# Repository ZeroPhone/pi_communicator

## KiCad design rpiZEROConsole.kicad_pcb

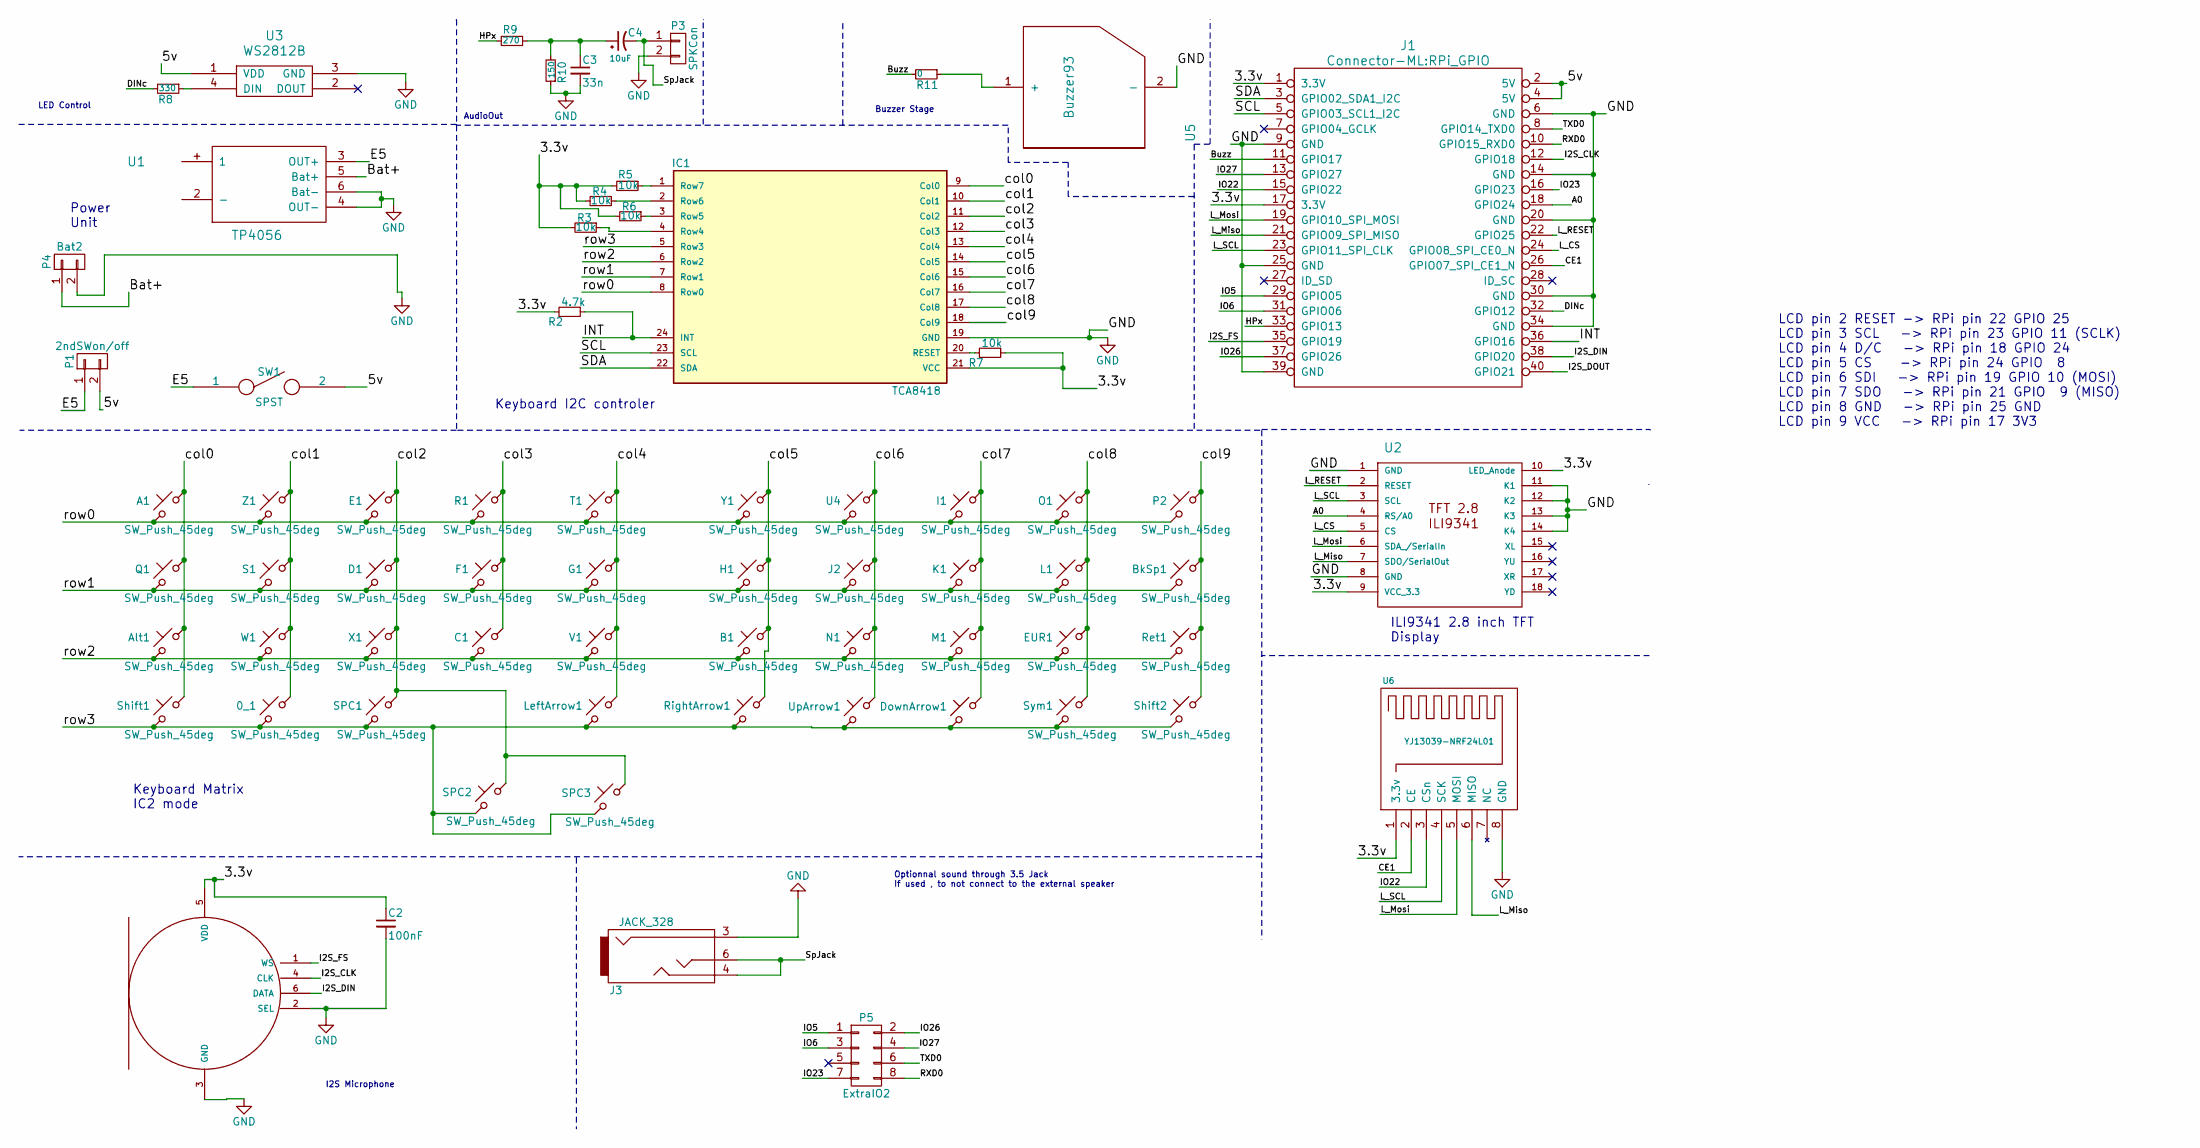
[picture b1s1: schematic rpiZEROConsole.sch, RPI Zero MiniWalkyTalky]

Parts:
0_1: SW_Push_45deg; SW_TP1003
A1: SW_Push_45deg; SW_TP1003
Alt1: SW_Push_45deg; SW_TP1003
B1: SW_Push_45deg; SW_TP1003
BkSp1: SW_Push_45deg; SW_TP1003
C1: SW_Push_45deg; SW_TP1003
C2: 100nF; C_1206_HandSoldering
C3: 33n; C_1206_HandSoldering
C4: 10uF; CP_Elec_6.3x5.3
D1: SW_Push_45deg; SW_TP1003
DownArrow1: SW_Push_45deg; SW_TP1003
E1: SW_Push_45deg; SW_TP1003
EUR1: SW_Push_45deg; SW_TP1003
F1: SW_Push_45deg; SW_TP1003
G1: SW_Push_45deg; SW_TP1003
H1: SW_Push_45deg; SW_TP1003
I1: SW_Push_45deg; SW_TP1003
IC1: TCA8418; TCA8418-WQFN-24-1EP_4x4mm
J1: Connector-ML:RPi_GPIO; Raspberry_Pi_Zero_SMD
J2: SW_Push_45deg; SW_TP1003
J3: JACK_328; Jack_JP328
K1: SW_Push_45deg; SW_TP1003
L1: SW_Push_45deg; SW_TP1003
LeftArrow1: SW_Push_45deg; SW_TP1003
M1: SW_Push_45deg; SW_TP1003
M2: MEMS_MIC_SPH0645LM4H-BI2S; MIC_SPH0645LM4H-B
N1: SW_Push_45deg; SW_TP1003
O1: SW_Push_45deg; SW_TP1003
P1: 2ndSWon/off; Socket_Strip_Straight_1x02_Pitch2.54mm
P2: SW_Push_45deg; SW_TP1003
P3: SPKCon; Socket_Strip_Straight_1x02_Pitch2.54mm
P4: Bat2; Socket_Strip_Straight_1x02_Pitch2.54mm
P5: ExtraIO2; 2x4SMD
Q1: SW_Push_45deg; SW_TP1003
R1: SW_Push_45deg; SW_TP1003
R2: 4.7k; R_1206_HandSoldering
R3, R4, R5, R6, R7: 10k; R_1206_HandSoldering
R8: 330; R_1206_HandSoldering
R9: 270; R_1206_HandSoldering
R10: 150; R_1206_HandSoldering
R11: 0; R_1206_HandSoldering
Ret1: SW_Push_45deg; SW_TP1003
RightArrow1: SW_Push_45deg; SW_TP1003
S1: SW_Push_45deg; SW_TP1003
SPC1, SPC2, SPC3: SW_Push_45deg; SW_TP1003
SW1: SPST; SW_SPDT_PCM12
Shift1, Shift2: SW_Push_45deg; SW_TP1003
Sym1: SW_Push_45deg; SW_TP1003
T1: SW_Push_45deg; SW_TP1003
U1: TP4056; TP4056-18650CMS
U2: ILI9341_28_18PINS; ILI9341_2.8
U3: WS2812B
U4: SW_Push_45deg; SW_TP1003
U5: Buzzer93; BuzzerActive2
U6: YJ13039-NRF24L01; YJ-13039-NRF24L01
UpArrow1: SW_Push_45deg; SW_TP1003
V1: SW_Push_45deg; SW_TP1003
W1: SW_Push_45deg; SW_TP1003
X1: SW_Push_45deg; SW_TP1003
Y1: SW_Push_45deg; SW_TP1003
Z1: SW_Push_45deg; SW_TP1003

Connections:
/3.3v: C2.1, IC1.21 (VCC), J1.1 (3.3V), J1.17 (3.3V), M2.5 (VDD), R2.2, R3.2, R4.2, R5.2, R6.2, R7.1, U2.9 (VCC_3.3), U2.10 (LED_Anode), U6.1 (3.3v)
/5v: J1.2 (5V), J1.4 (5V), P1.2, SW1.2, U3.1 (VDD); also elsewhere on the board
/A0: J1.18 (GPIO24), U2.4 (RS/A0)
/Bat+: P4.1, U1.5 (Bat+); also elsewhere on the board
/Buzz: J1.11 (GPIO17), R11.2
/CE1: J1.26 (GPIO07_SPI_CE1_N), U6.2 (CE)
/DINc: J1.32 (GPIO12), R8.2
/E5: P1.1, SW1.1, U1.3 (OUT+); also elsewhere on the board
/HPx: J1.33 (GPIO13), R9.2
/I2S_CLK: J1.12 (GPIO18), M2.4 (CLK)
/I2S_DIN: J1.38 (GPIO20), M2.6 (DATA)
/I2S_FS: J1.35 (GPIO19), M2.1 (WS)
/INT: IC1.24 (INT), J1.36 (GPIO16), R2.1
/IO5: J1.29 (GPIO05), P5.1
/IO6: J1.31 (GPIO06), P5.3
/IO22: J1.15 (GPIO22), U6.3 (CSn)
/IO23: J1.16 (GPIO23), P5.7
/IO26: J1.37 (GPIO26), P5.2
/IO27: J1.13 (GPIO27), P5.4
/L_CS: J1.24 (GPIO08_SPI_CE0_N), U2.5 (CS)
/L_Miso: J1.21 (GPIO09_SPI_MISO), U2.7 (SDO/SerialOut), U6.6 (MISO)
/L_Mosi: J1.19 (GPIO10_SPI_MOSI), U2.6 (SDA_/SerialIn), U6.5 (MOSI)
/L_RESET: J1.22 (GPIO25), U2.2 (RESET)
/L_SCL: J1.23 (GPIO11_SPI_CLK), U2.3 (SCL), U6.4 (SCK)
/RXD0: J1.10 (GPIO15_RXD0), P5.8
/SCL: IC1.23 (SCL), J1.5 (GPIO03_SCL1_I2C)
/SDA: IC1.22 (SDA), J1.3 (GPIO02_SDA1_I2C)
/SpJack: C4.2, J3.4, J3.6, P3.1
/TXD0: J1.8 (GPIO14_TXD0), P5.6
/col0: A1.1, Alt1.1, IC1.9 (Col0), Q1.1, Shift1.1
/col1: 0_1.1, IC1.10 (Col1), S1.1, W1.1, Z1.1
/col2: D1.1, E1.1, IC1.11 (Col2), SPC1.1, SPC2.1, SPC3.1, X1.1
/col3: C1.1, F1.1, IC1.12 (Col3), R1.1
/col4: G1.1, IC1.13 (Col4), LeftArrow1.1, T1.1, V1.1
/col5: B1.1, H1.1, IC1.14 (Col5), RightArrow1.1, Y1.1
/col6: IC1.15 (Col6), J2.1, N1.1, U4.1, UpArrow1.1
/col7: DownArrow1.1, I1.1, IC1.16 (Col7), K1.1, M1.1
/col8: EUR1.1, IC1.17 (Col8), L1.1, O1.1, Sym1.1
/col9: BkSp1.1, IC1.18 (Col9), P2.1, Ret1.1, Shift2.1
/row0: A1.2, E1.2, I1.2, IC1.8 (Row0), O1.2, P2.2, R1.2, T1.2, U4.2, Y1.2, Z1.2
/row1: BkSp1.2, D1.2, F1.2, G1.2, H1.2, IC1.7 (Row1), J2.2, K1.2, L1.2, Q1.2, S1.2
/row2: Alt1.2, B1.2, C1.2, EUR1.2, IC1.6 (Row2), M1.2, N1.2, Ret1.2, V1.2, W1.2, X1.2
/row3: 0_1.2, DownArrow1.2, IC1.5 (Row3), LeftArrow1.2, RightArrow1.2, SPC1.2, SPC2.2, SPC3.2, Shift1.2, Shift2.2, Sym1.2, UpArrow1.2
GND: C2.2, C3.2, IC1.19 (GND), J1.6 (GND), J1.9 (GND), J1.14 (GND), J1.20 (GND), J1.25 (GND), J1.30 (GND), J1.34 (GND), J1.39 (GND), J3.3, M2.2 (SEL), M2.3 (GND), M2.P$1 (GND), P3.2, P4.2, R10.1, U1.4 (OUT-), U1.6 (Bat-), U2.1 (GND), U2.8 (GND), U2.11 (K1), U2.12 (K2), U2.13 (K3), U2.14 (K4), U3.3 (GND), U5.2 (-), U6.8 (GND); also elsewhere on the board
unnamed: C3.1, C4.1, R9.1, R10.2
unnamed: IC1.1 (Row7), R5.1
unnamed: IC1.2 (Row6), R4.1
unnamed: IC1.3 (Row5), R6.1
unnamed: IC1.4 (Row4), R3.1
unnamed: IC1.20 (RESET), R7.2
unnamed: R8.1, U3.4 (DIN)
unnamed: R11.1, U5.1 (+)

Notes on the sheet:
Power Unit
Keyboard Matrix IC2 mode
Keyboard I2C controler
ILI9341 2.8 inch TFT Display
LCD pin 2 RESET -> RPi pin 22 GPIO 25 LCD pin 3 SCL -> RPi pin 23 GPIO 11 (SCLK) LCD pin 4 D/C -> RPi pin 18 GPIO 24 LCD pin 5 CS -> RPi pin 24 GPIO 8 LCD pin 6 SDI -> RPi pin 19 GPIO 10 (MOSI) LCD pin 7 SDO -> RPi pin 21 GPIO 9 (MISO) LCD pin 8 GND -> RPi pin 25 GND LCD pin 9 VCC -> RPi pin 17 3V3
LED Control
Buzzer Stage
AudioOut
I2S Microphone
Optionnal sound through 3.5 Jack If used , to not connect to the external speaker

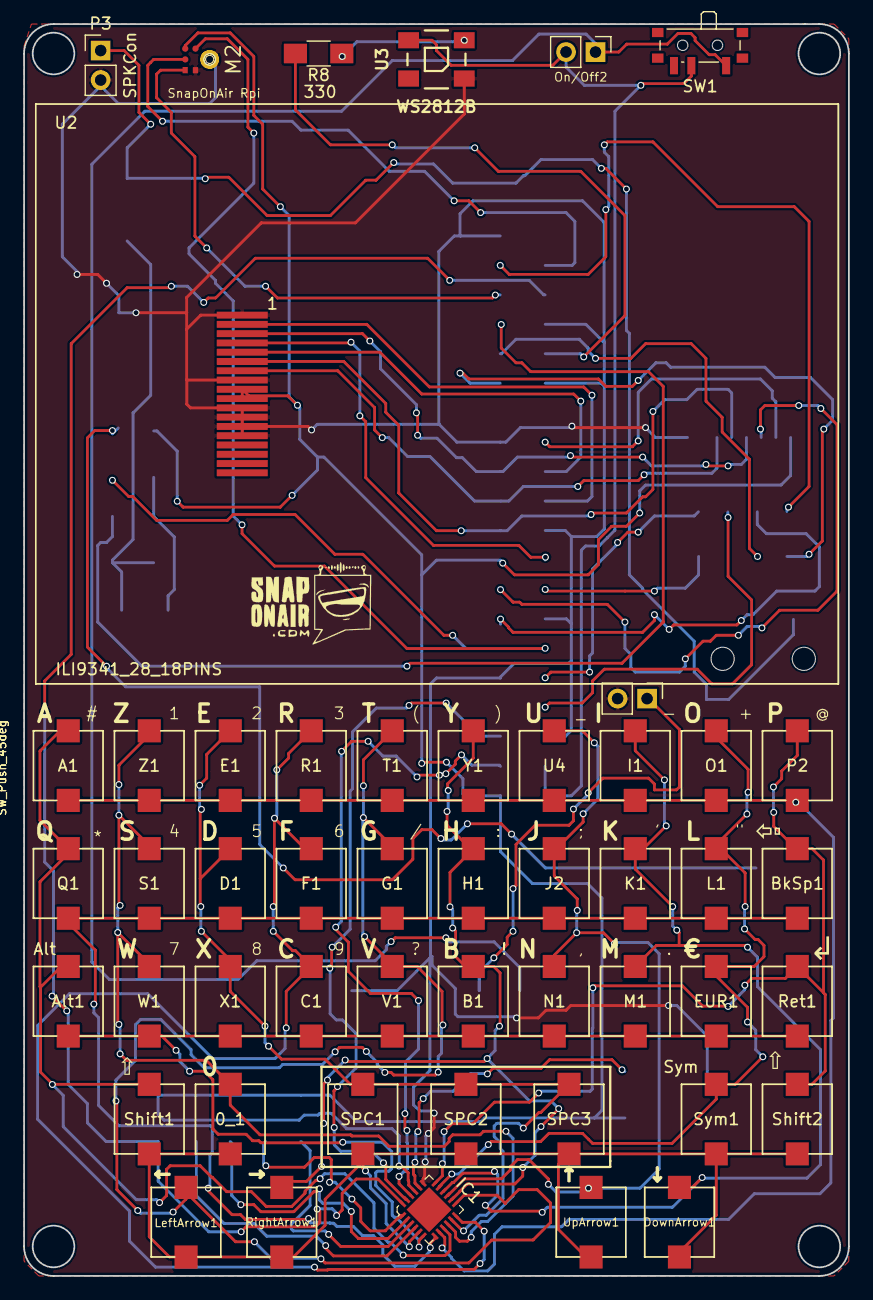
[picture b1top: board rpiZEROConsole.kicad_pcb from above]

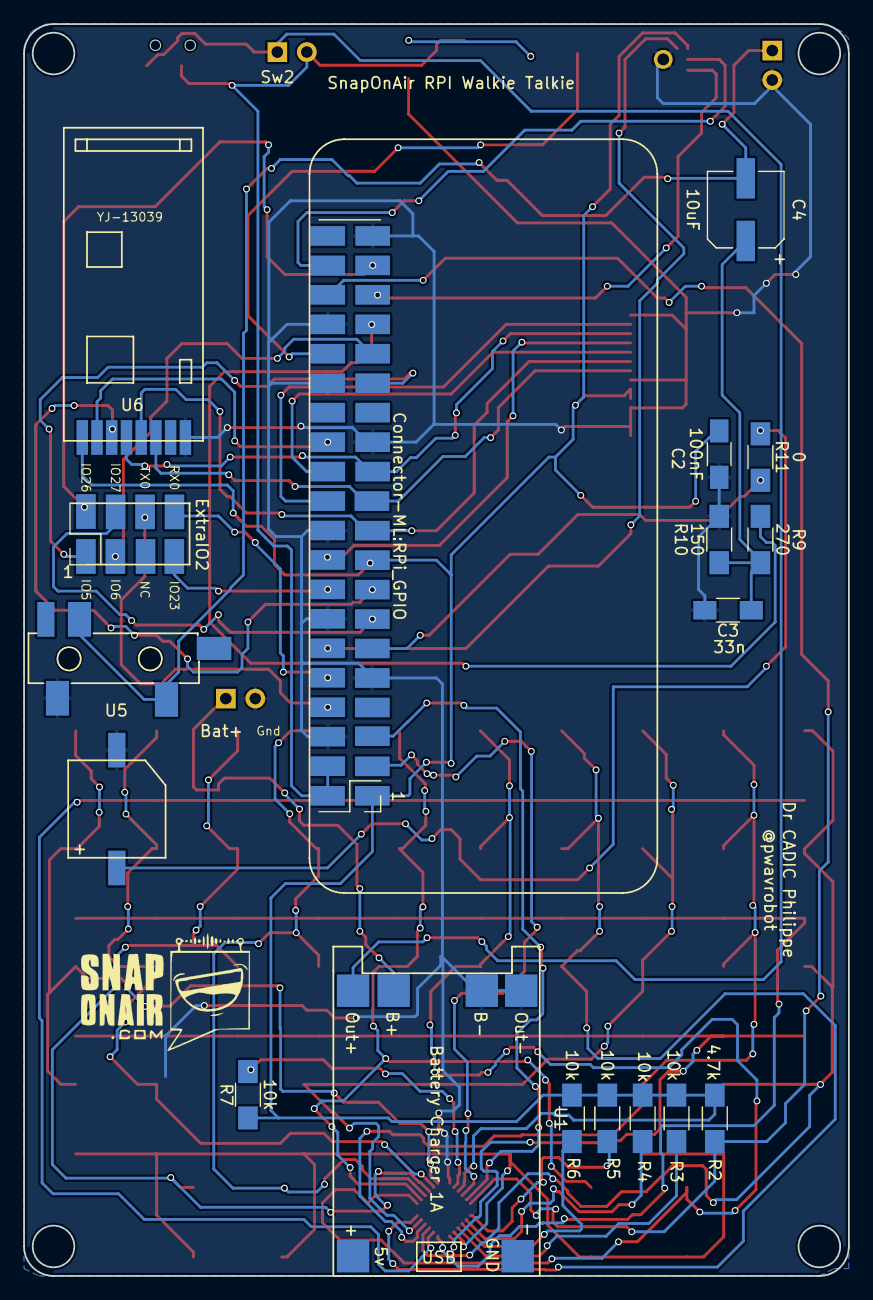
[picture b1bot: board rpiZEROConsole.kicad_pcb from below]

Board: 2 copper layers, 71.1 x 108.0 mm, 68 parts (18 on the bottom side), 52 nets.

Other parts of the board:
Bat+: Bat2; Socket_Strip_Straight_1x02_Pitch2.54mm
On/Off2: 2ndSWon/off; Socket_Strip_Straight_1x02_Pitch2.54mm

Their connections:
/5v: On/Off2.2; also elsewhere on the board
/Bat+: Bat+.1; also elsewhere on the board
/E5: On/Off2.1; also elsewhere on the board
GND: Bat+.2; also elsewhere on the board

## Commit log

2019-12-26 Initial commit + added .gitignore for KiCad files
